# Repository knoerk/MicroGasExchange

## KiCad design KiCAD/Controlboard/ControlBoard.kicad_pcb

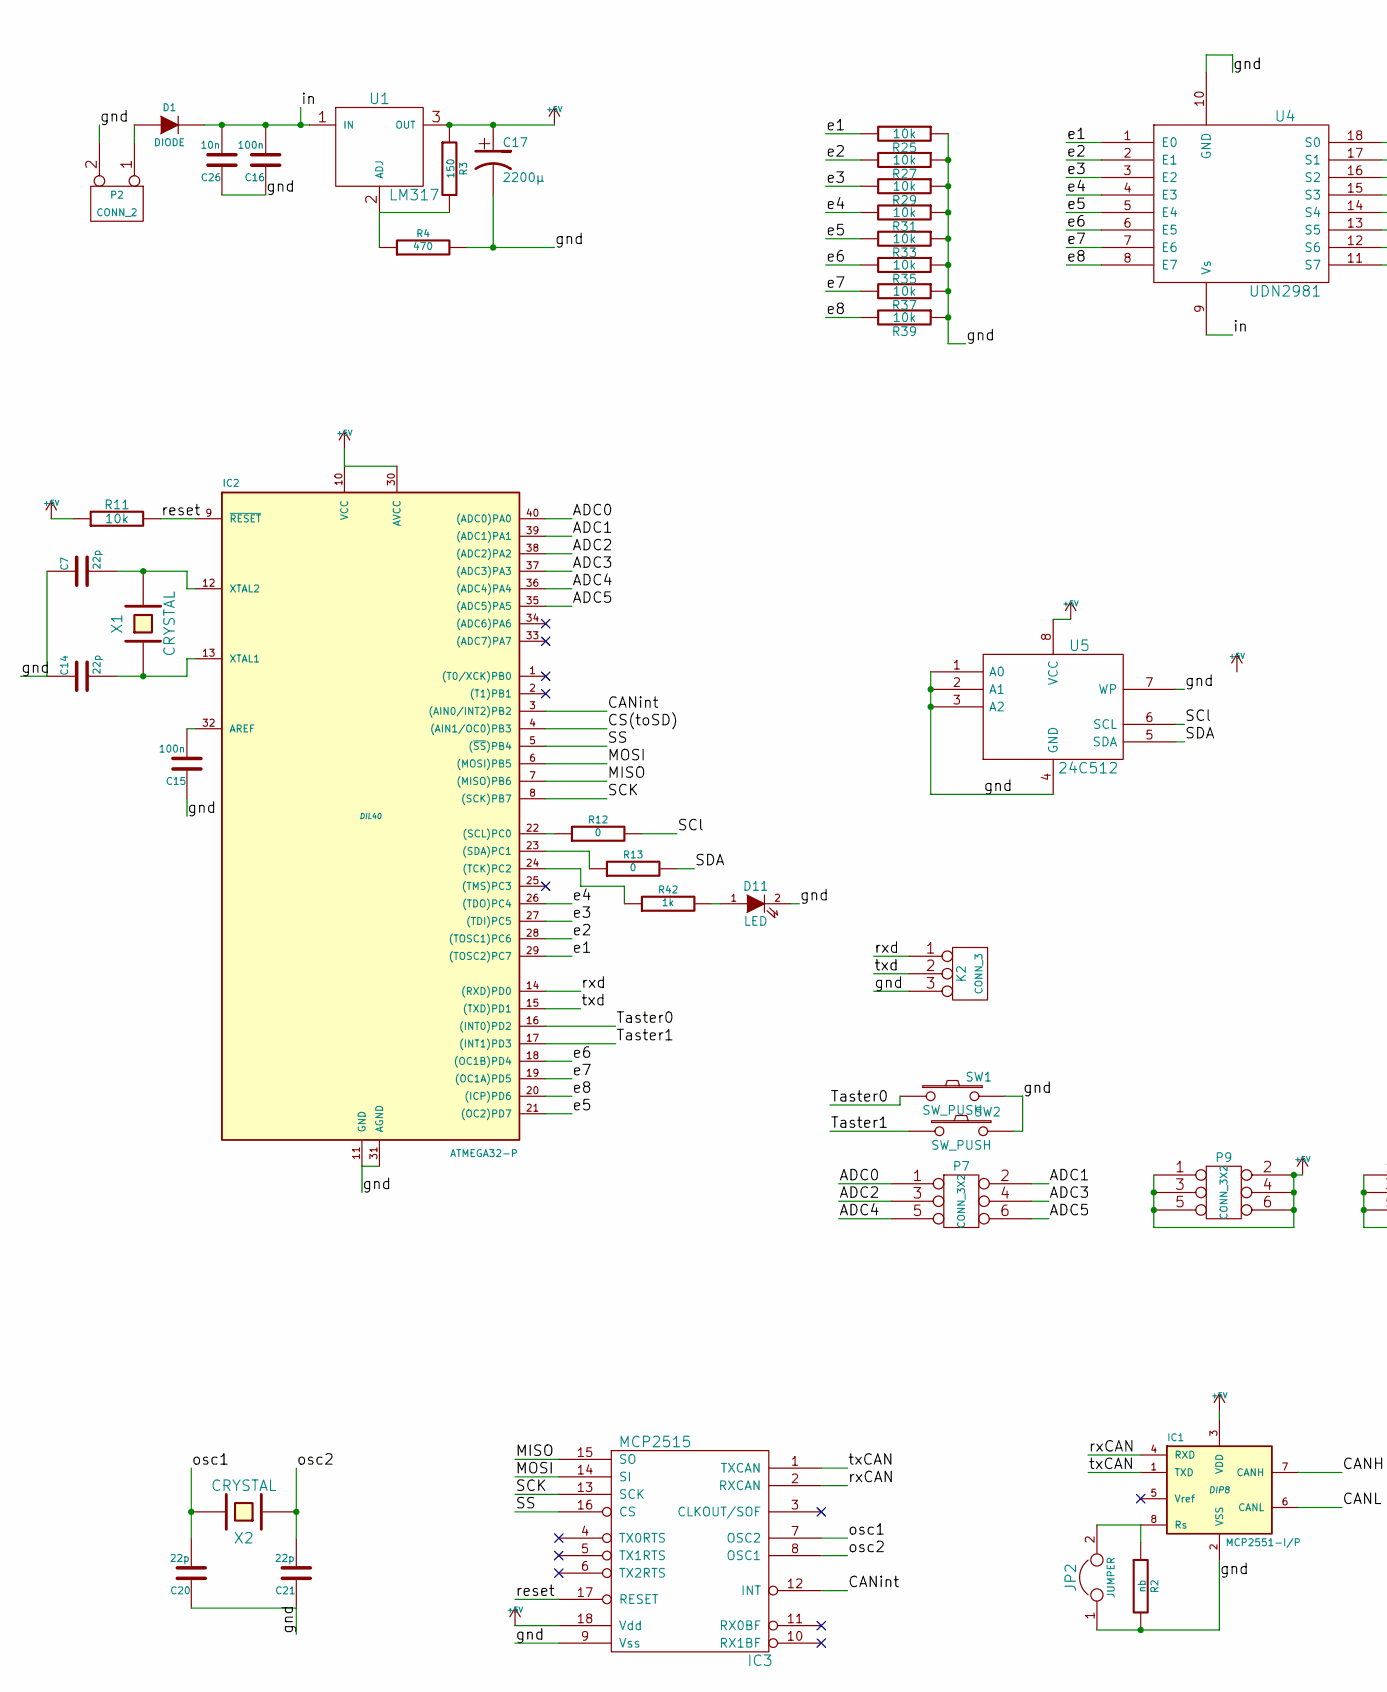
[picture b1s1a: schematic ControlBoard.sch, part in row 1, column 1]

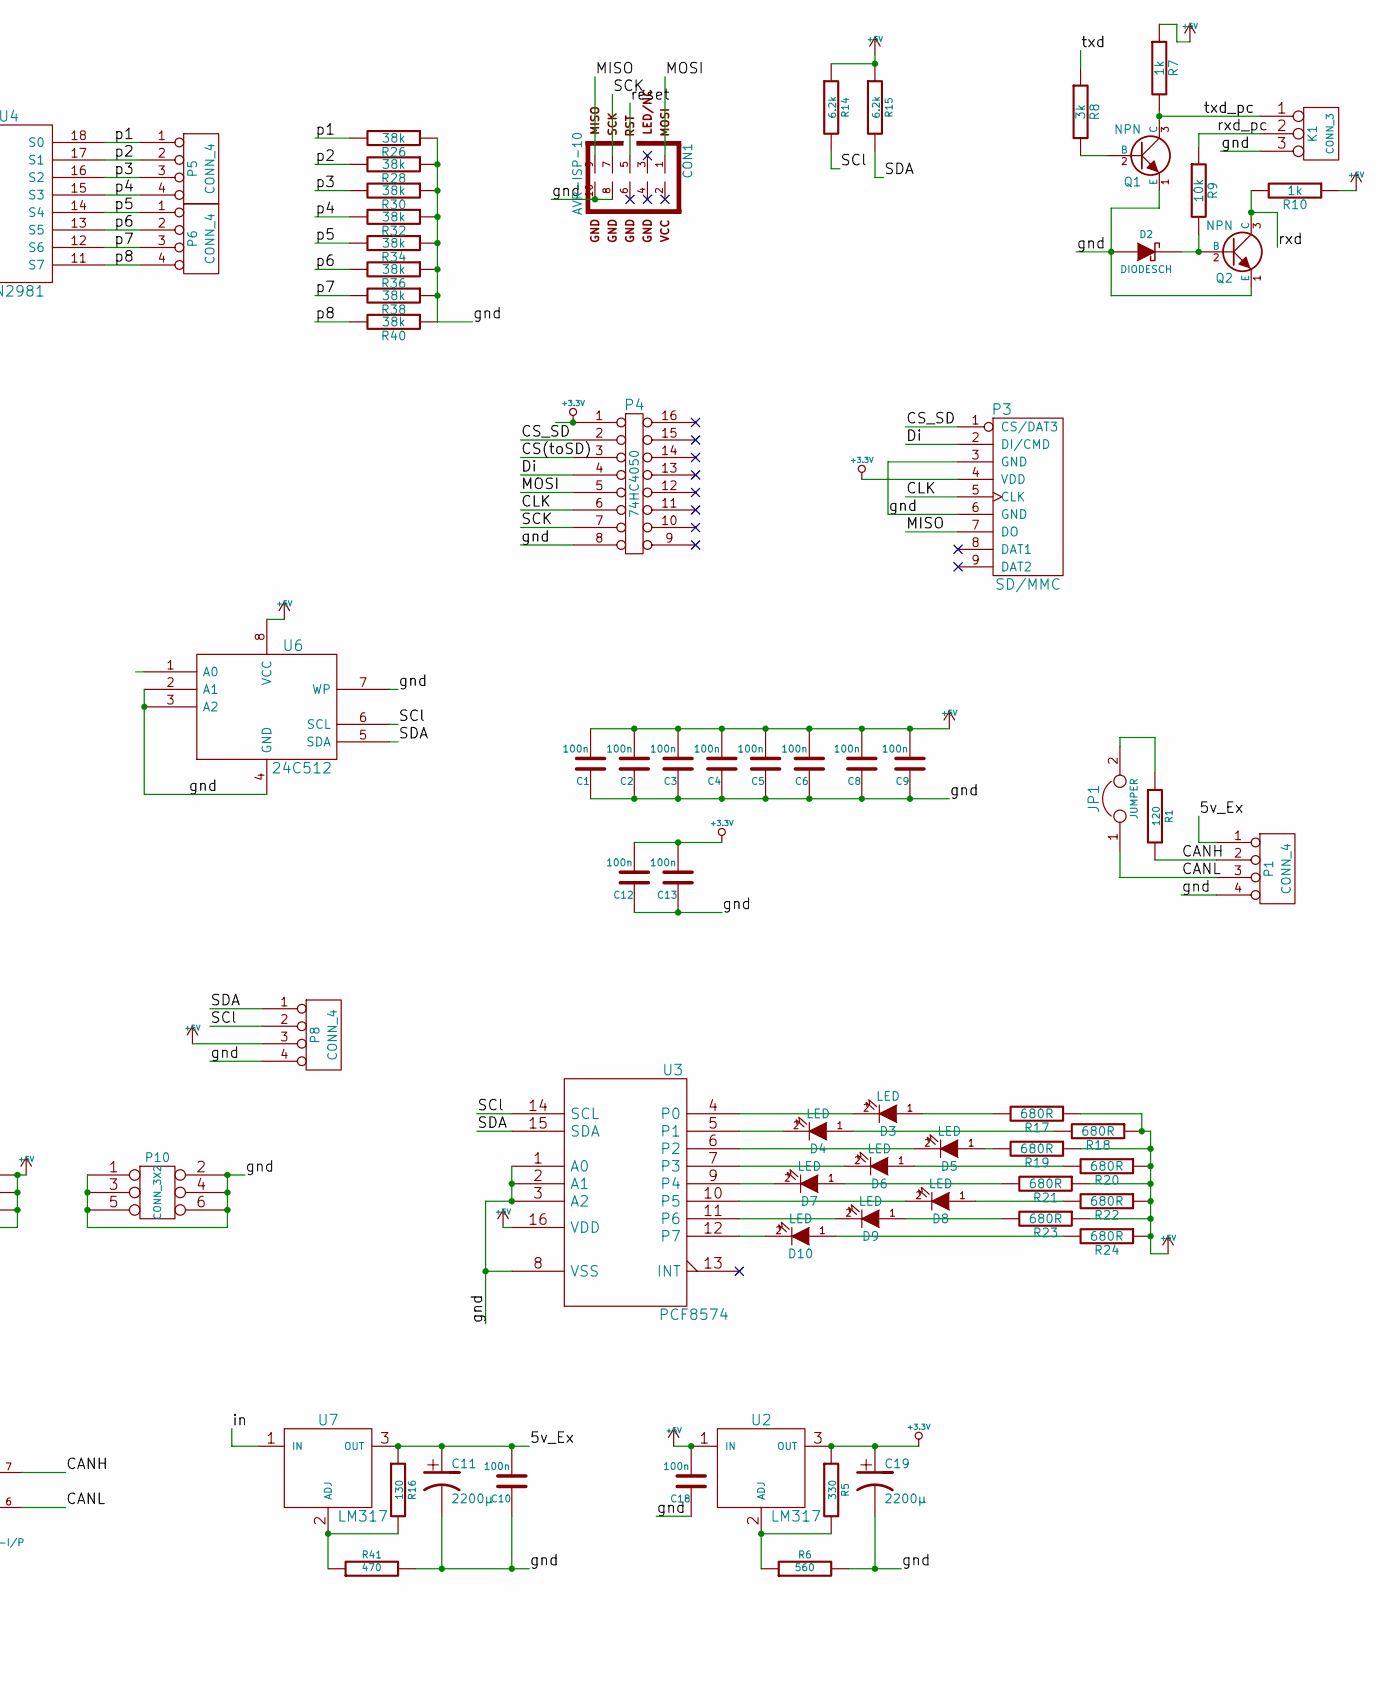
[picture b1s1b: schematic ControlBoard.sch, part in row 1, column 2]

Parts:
C1, C2, C3, C4, C5, C6, C8, C9, C10, C12, C13, C15, C16, C18: 100n
C7, C14, C20, C21: 22p
C11, C17, C19: 2200µ
C26: 10n
CON1: AVR-ISP-10
D1: DIODE
D2: DIODESCH
D3, D4, D5, D6, D7, D8, D9, D10, D11: LED
IC1: MCP2551-I/P; DIP8
IC2: ATMEGA32-P; DIL40
IC3: MCP2515
JP1, JP2: JUMPER
K1, K2: CONN_3
P1, P5, P6, P8: CONN_4
P2: CONN_2
P3: SD/MMC
P4: 74HC4050
P7, P9, P10: CONN_3X2
Q1, Q2: NPN
R1: 120
R2: nb
R3: 150
R4, R41: 470
R5: 330
R6: 560
R7, R10: 1k
R8: 3k
R9, R11, R25, R27, R29, R31, R33, R35, R37, R39: 10k
R12, R13: 0
R14, R15: 6.2k
R16: 130
R17, R18, R19, R20, R21, R22, R23, R24: 680R
R26, R28, R30, R32, R34, R36, R38, R40: 38k
R42: 1k
SW1, SW2: SW_PUSH
U1, U2, U7: LM317
U3: PCF8574
U4: UDN2981
U5, U6: 24C512
X1, X2: CRYSTAL

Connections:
+3.3V: C12.2, C13.2, C19.1, P3.4 (VDD), P4.1, R5.1, U2.3 (OUT)
+5V: C1.2, C2.2, C3.2, C4.2, C5.2, C6.2, C8.2, C9.2, C17.1, C18.2, IC1.3 (VDD), IC2.10 (VCC), IC2.30 (AVCC), IC3.18 (Vdd), P8.3, P9.1, P9.2, P9.3, P9.4, P9.5, P9.6, R3.1, R7.1, R10.1, R11.1, R14.1, R15.1, R17.1, R18.1, R19.1, R20.1, R21.1, R22.1, R23.1, R24.1, U1.3 (OUT), U2.1 (IN), U3.16 (VDD), U5.8 (VCC), U6.1 (A0), U6.8 (VCC)
/5v_Ex: C10.2, C11.1, P1.1, R16.1, U7.3 (OUT)
/ADC0: IC2.40 ((ADC0)PA0), P7.1
/ADC1: IC2.39 ((ADC1)PA1), P7.2
/ADC2: IC2.38 ((ADC2)PA2), P7.3
/ADC3: IC2.37 ((ADC3)PA3), P7.4
/ADC4: IC2.36 ((ADC4)PA4), P7.5
/ADC5: IC2.35 ((ADC5)PA5), P7.6
/CANH: IC1.7 (CANH), P1.2, R1.2
/CANL: IC1.6 (CANL), JP1.1, P1.3
/CANint: IC2.3 ((AIN0/INT2)PB2), IC3.12 (INT)
/CLK: P3.5 (CLK), P4.6
/CS(toSD): IC2.4 ((AIN1/OC0)PB3), P4.3
/CS_SD: P3.1 (CS/DAT3), P4.2
/Di: P3.2 (DI/CMD), P4.4
/MISO: CON1.9, IC2.7 ((MISO)PB6), IC3.15 (SO), P3.7 (DO)
/MOSI: CON1.1, IC2.6 ((MOSI)PB5), IC3.14 (SI), P4.5
/SCK: CON1.7, IC2.8 ((SCK)PB7), IC3.13 (SCK), P4.7
/SCl: P8.2, R12.2, R14.2, U3.14 (SCL), U5.6 (SCL), U6.6 (SCL)
/SDA: P8.1, R13.2, R15.2, U3.15 (SDA), U5.5 (SDA), U6.5 (SDA)
/SS: IC2.5 ((~SS~)PB4), IC3.16 (CS)
/Taster0: IC2.16 ((INT0)PD2), SW1.1
/Taster1: IC2.17 ((INT1)PD3), SW2.1
/e0: IC2.29 ((TOSC2)PC7), R25.2, U4.1 (E0)
/e1: IC2.28 ((TOSC1)PC6), R27.2, U4.2 (E1)
/e2: IC2.27 ((TDI)PC5), R29.2, U4.3 (E2)
/e3: IC2.26 ((TDO)PC4), R31.2, U4.4 (E3)
/e4: IC2.21 ((OC2)PD7), R33.2, U4.5 (E4)
/e5: IC2.18 ((OC1B)PD4), R35.2, U4.6 (E5)
/e6: IC2.19 ((OC1A)PD5), R37.2, U4.7 (E6)
/e7: IC2.20 ((ICP)PD6), R39.2, U4.8 (E7)
/gnd: C1.1, C2.1, C3.1, C4.1, C5.1, C6.1, C7.1, C8.1, C9.1, C10.1, C11.2, C12.1, C13.1, C14.1, C15.1, C16.1, C17.2, C18.1, C19.2, C20.1, C21.1, C26.1, CON1.8, CON1.10, D2.1 (A), D11.2 (K), IC1.2 (VSS), IC2.11 (GND), IC2.31 (AGND), IC3.9 (Vss), JP2.1, K1.3, K2.3, P1.4, P2.2 (PM), P3.3 (GND), P3.6 (GND), P4.8, P8.4, P10.1, P10.2, P10.3, P10.4, P10.5, P10.6, Q1.1 (E), Q2.1 (E), R2.2, R4.2, R6.2, R25.1, R26.1, R27.1, R28.1, R29.1, R30.1, R31.1, R32.1, R33.1, R34.1, R35.1, R36.1, R37.1, R38.1, R39.1, R40.1, R41.2, SW1.2, SW2.2, U3.1 (A0), U3.2 (A1), U3.3 (A2), U3.8 (VSS), U4.10 (GND), U5.1 (A0), U5.2 (A1), U5.3 (A2), U5.4 (GND), U5.7 (WP), U6.2 (A1), U6.3 (A2), U6.4 (GND), U6.7 (WP)
/in: C16.2, C26.2, D1.2 (K), U1.1 (IN), U4.9 (Vs), U7.1 (IN)
/osc1: C20.2, IC3.7 (OSC2), X2.2
/osc2: C21.2, IC3.8 (OSC1), X2.1
/p1: P5.1, R26.2, U4.18 (S0)
/p2: P5.2, R28.2, U4.17 (S1)
/p3: P5.3, R30.2, U4.16 (S2)
/p4: P5.4, R32.2, U4.15 (S3)
/p5: P6.1, R34.2, U4.14 (S4)
/p6: P6.2, R36.2, U4.13 (S5)
/p7: P6.3, R38.2, U4.12 (S6)
/p8: P6.4, R40.2, U4.11 (S7)
/reset: CON1.5, IC2.9 (~RESET), IC3.17 (RESET), R11.2
/rxCAN: IC1.4 (RXD), IC3.2 (RXCAN)
/rxd: IC2.14 ((RXD)PD0), K2.1, Q2.3 (C), R10.2
/rxd_pc: K1.2 (PM), R9.1
/txCAN: IC1.1 (TXD), IC3.1 (TXCAN)
/txd: IC2.15 ((TXD)PD1), K2.2 (PM), R8.1
/txd_pc: K1.1, Q1.3 (C), R7.2
unnamed: D6.2 (K), U3.7 (P3)
unnamed: D7.1 (A), R21.2
unnamed: D7.2 (K), U3.9 (P4)
unnamed: D8.1 (A), R22.2
unnamed: D8.2 (K), U3.10 (P5)
unnamed: D9.1 (A), R23.2
unnamed: D9.2 (K), U3.11 (P6)
unnamed: D10.1 (A), R24.2
unnamed: D10.2 (K), U3.12 (P7)
unnamed: D3.2 (K), U3.4 (P0)
unnamed: D4.2 (K), U3.5 (P1)
unnamed: D5.2 (K), U3.6 (P2)
unnamed: D3.1 (A), R17.2
unnamed: D4.1 (A), R18.2
unnamed: D5.1 (A), R19.2
unnamed: D6.1 (A), R20.2
unnamed: IC2.22 ((SCL)PC0), R12.1
unnamed: IC2.23 ((SDA)PC1), R13.1
unnamed: IC2.24 ((TCK)PC2), R42.1
unnamed: D11.1 (A), R42.2
unnamed: R16.2, R41.1, U7.2 (ADJ)
unnamed: JP1.2, R1.1
unnamed: R3.2, R4.1, U1.2 (ADJ)
unnamed: R5.2, R6.1, U2.2 (ADJ)
unnamed: C14.2, IC2.13 (XTAL1), X1.1
unnamed: C7.2, IC2.12 (XTAL2), X1.2
unnamed: D1.1 (A), P2.1
unnamed: Q1.2 (B), R8.2
unnamed: D2.2 (K), Q2.2 (B), R9.2
unnamed: IC1.8 (Rs), JP2.2, R2.1
unnamed: C15.2, IC2.32 (AREF)

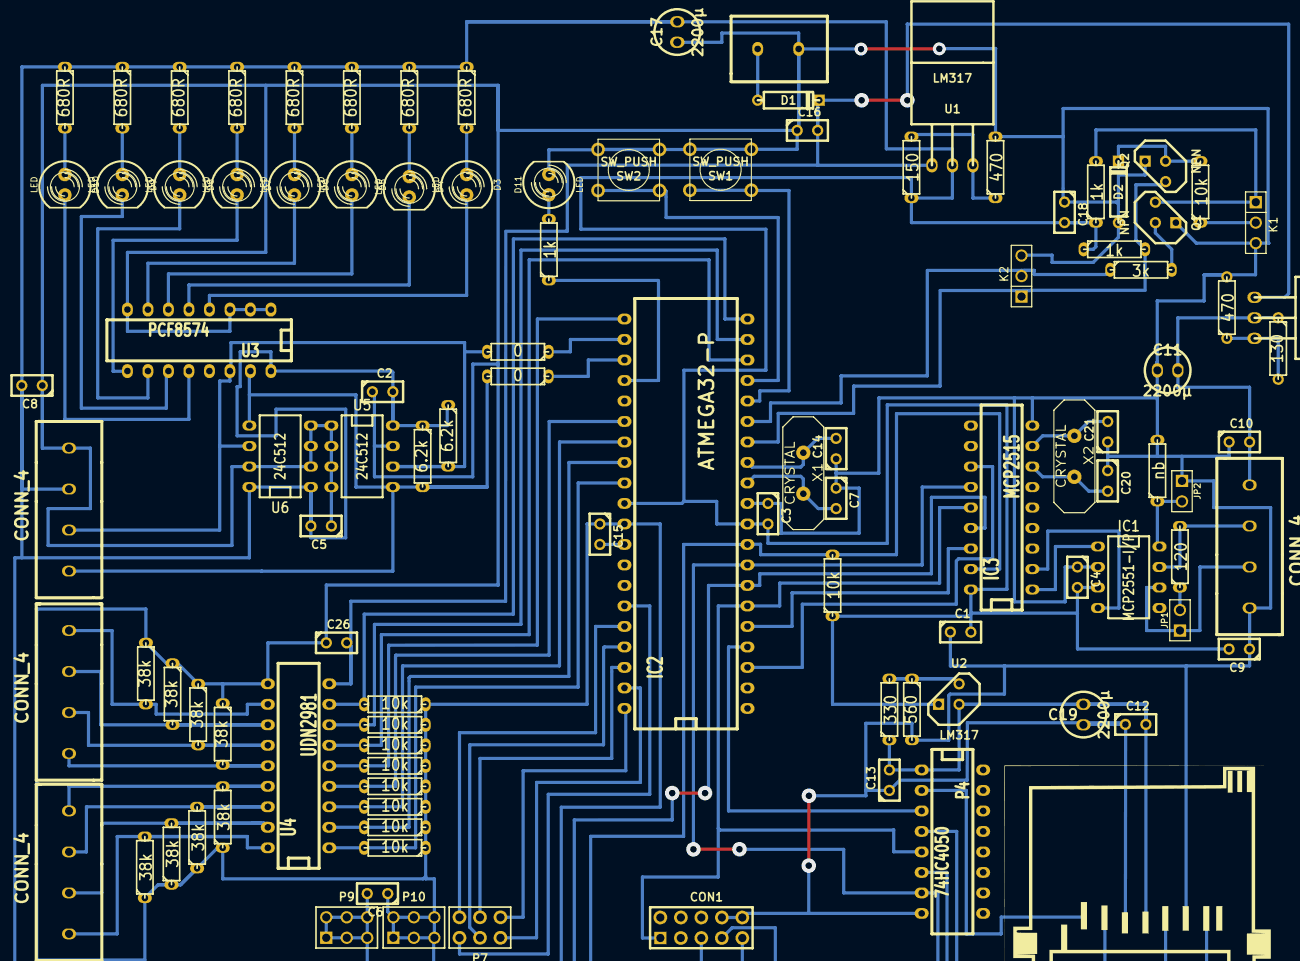
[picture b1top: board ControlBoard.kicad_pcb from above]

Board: 2 copper layers, 106 parts (0 on the bottom side), 82 nets.

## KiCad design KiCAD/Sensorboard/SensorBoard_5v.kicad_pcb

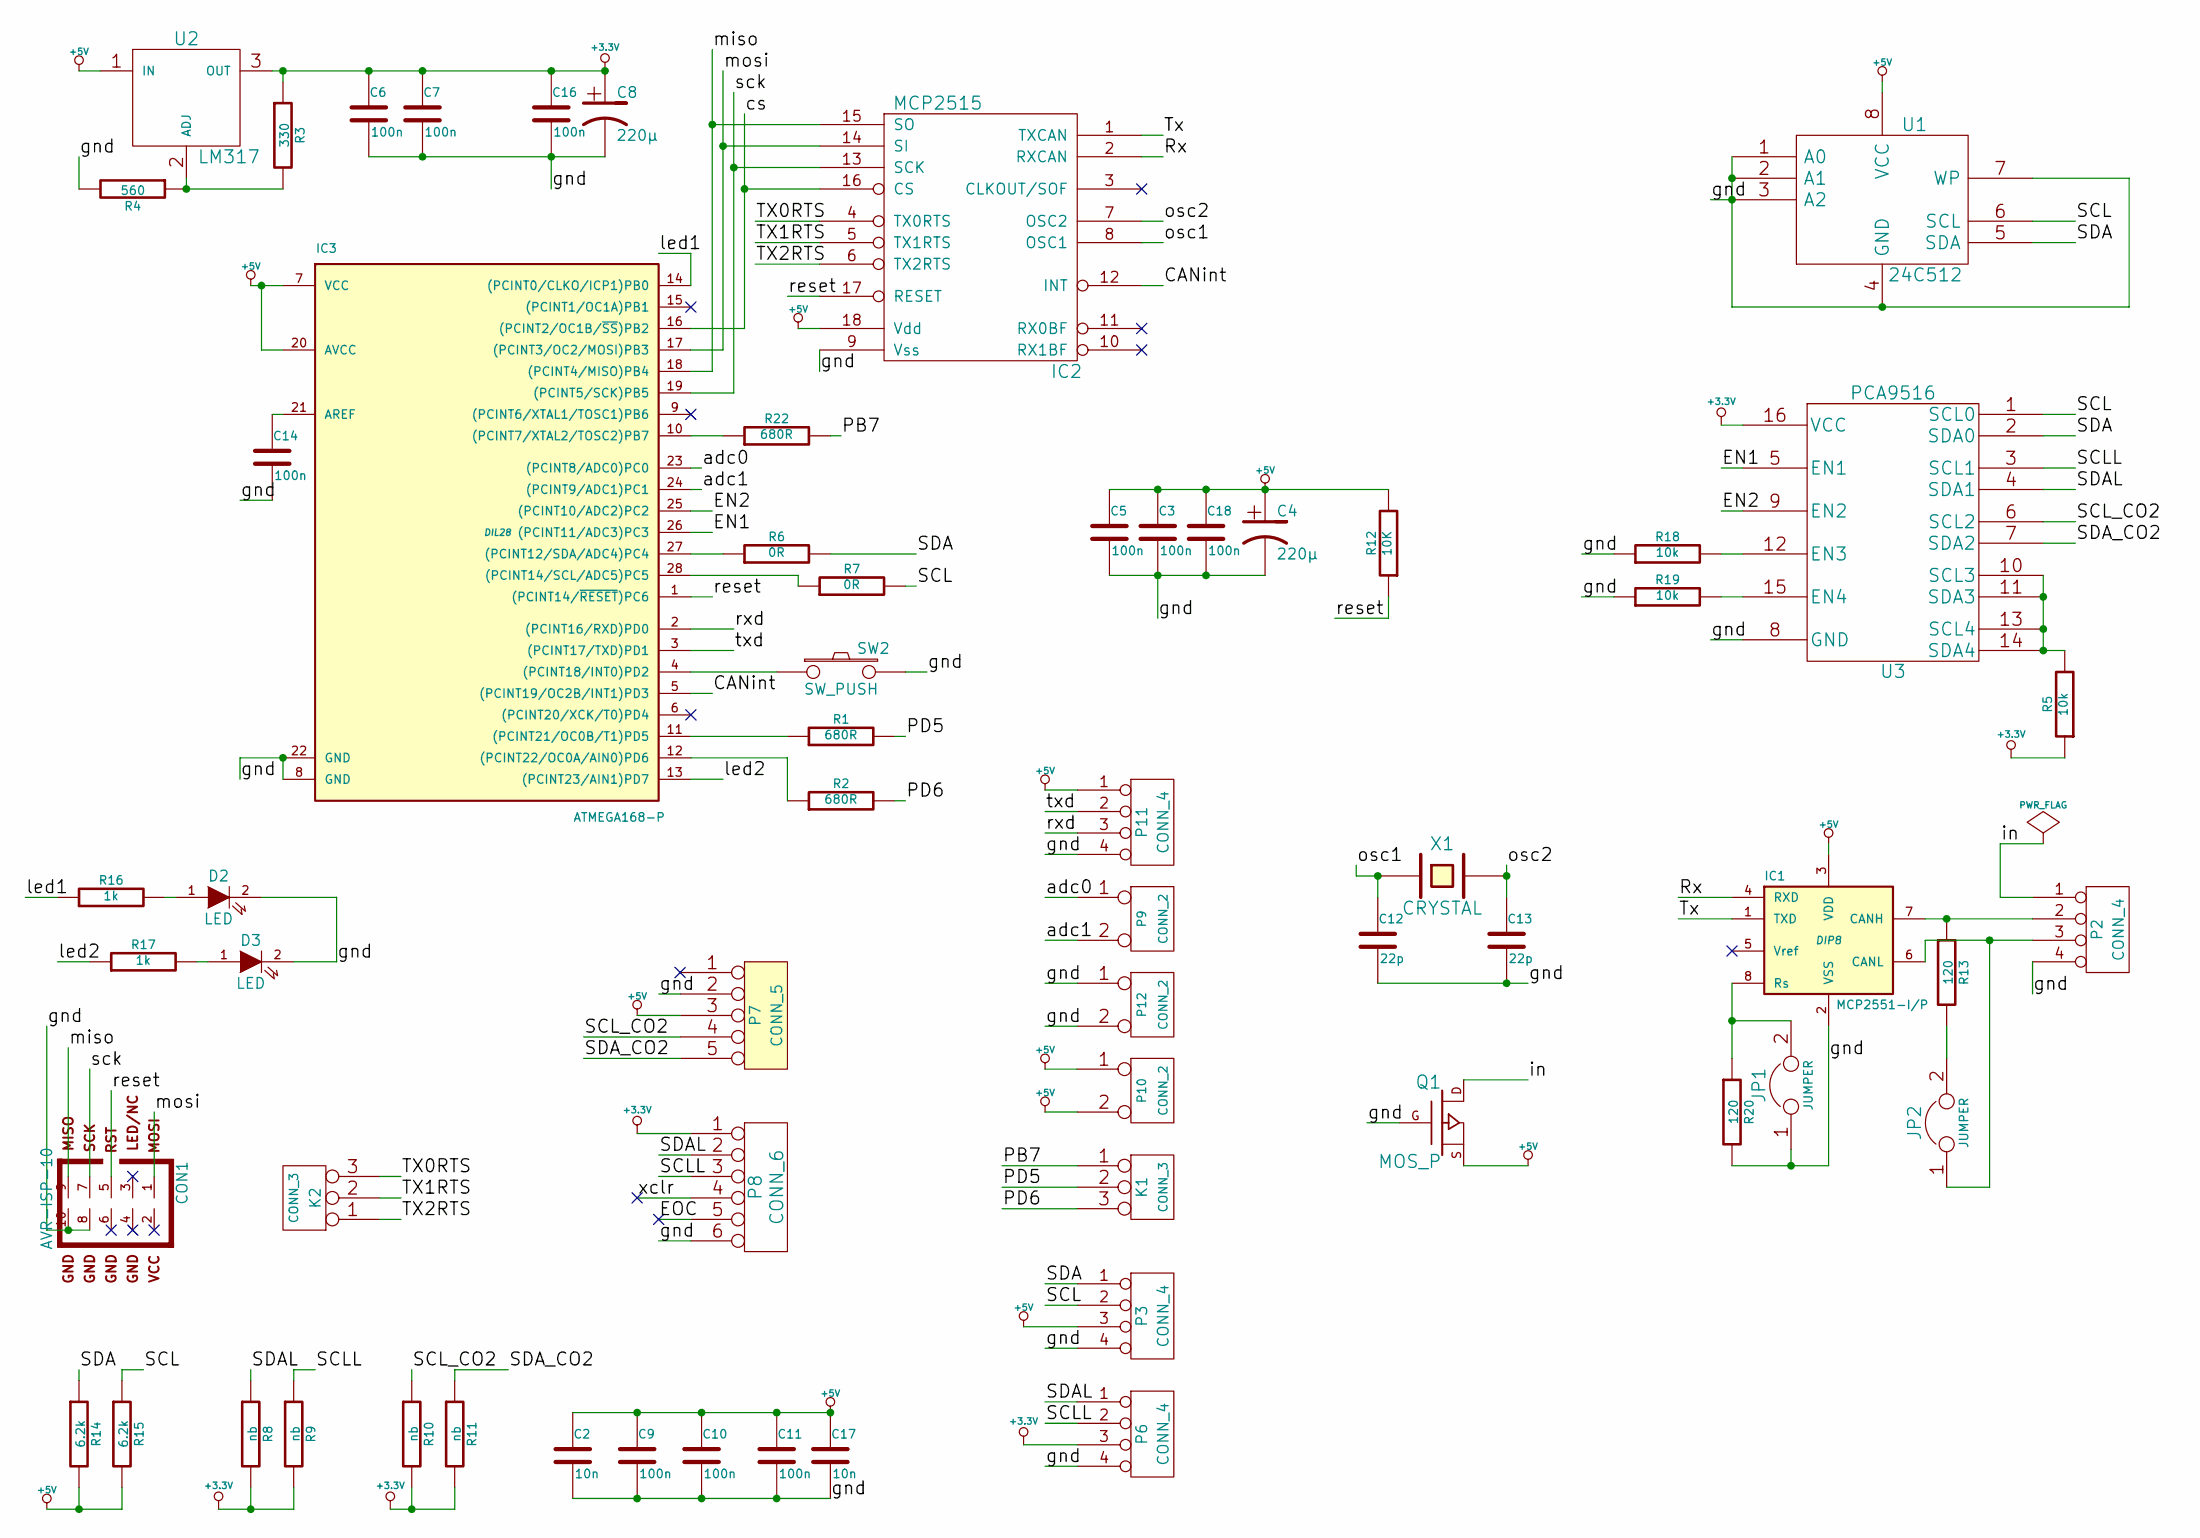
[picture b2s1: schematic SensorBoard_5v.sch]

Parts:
C2, C17: 10n
C3, C5, C6, C7, C9, C10, C11, C14, C16, C18: 100n
C4, C8: 220µ
C12, C13: 22p
CON1: AVR-ISP-10
D2, D3: LED
IC1: MCP2551-I/P; DIP8
IC2: MCP2515
IC3: ATMEGA168-P; DIL28
JP1, JP2: JUMPER
K1, K2: CONN_3
P2, P3, P6, P11: CONN_4
P7: CONN_5
P8: CONN_6
P9, P10, P12: CONN_2
Q1: MOS_P
R1, R2, R22: 680R
R3: 330
R4: 560
R5, R18, R19: 10k
R6, R7: 0R
R8, R9, R10, R11: nb
R12: 10K
R13, R20: 120
R14, R15: 6.2k
R16, R17: 1k
SW2: SW_PUSH
U1: 24C512
U2: LM317
U3: PCA9516
X1: CRYSTAL

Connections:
+3.3V: C6.1, C7.1, C8.1, C16.1, P6.3, P8.1, R3.1, R5.1, R8.2, R9.2, R10.2, R11.2, U2.3 (OUT), U3.16 (VCC)
+5V: C2.1, C3.1, C4.1, C5.1, C9.1, C10.1, C11.1, C17.1, C18.1, IC1.3 (VDD), IC2.18 (Vdd), IC3.7 (VCC), IC3.20 (AVCC), P3.3, P7.3, P10.1, P10.2 (PM), P11.1, Q1.S, R12.2, R14.2, R15.2, U1.8 (VCC), U2.1 (IN)
/CANint: IC2.12 (INT), IC3.5 ((PCINT19/OC2B/INT1)PD3)
/EN1: IC3.26 ((PCINT11/ADC3)PC3), U3.5 (EN1)
/EN2: IC3.25 ((PCINT10/ADC2)PC2), U3.9 (EN2)
/PB7: K1.1, R22.2
/PD5: K1.2 (PM), R1.2
/PD6: K1.3, R2.2
/Rx: IC1.4 (RXD), IC2.2 (RXCAN)
/SCL: P3.2, R7.2, R15.1, U1.6 (SCL), U3.1 (SCL0)
/SCLL: P6.2, P8.3, R9.1, U3.3 (SCL1)
/SCL_CO2: P7.4, R10.1, U3.6 (SCL2)
/SDA: P3.1, R6.2, R14.1, U1.5 (SDA), U3.2 (SDA0)
/SDAL: P6.1, P8.2, R8.1, U3.4 (SDA1)
/SDA_CO2: P7.5, R11.1, U3.7 (SDA2)
/TX0RTS: IC2.4 (TX0RTS), K2.3
/TX1RTS: IC2.5 (TX1RTS), K2.2 (PM)
/TX2RTS: IC2.6 (TX2RTS), K2.1
/Tx: IC1.1 (TXD), IC2.1 (TXCAN)
/adc0: IC3.23 ((PCINT8/ADC0)PC0), P9.1
/adc1: IC3.24 ((PCINT9/ADC1)PC1), P9.2 (PM)
/cs: IC2.16 (CS), IC3.16 ((PCINT2/OC1B/~SS~)PB2)
/gnd: C2.2, C3.2, C4.2, C5.2, C6.2, C7.2, C8.2, C9.2, C10.2, C11.2, C12.2, C13.2, C14.2, C16.2, C17.2, C18.2, CON1.8, CON1.10, D2.2 (K), D3.2 (K), IC1.2 (VSS), IC2.9 (Vss), IC3.8 (GND), IC3.22 (GND), JP1.1, P2.4, P3.4, P6.4, P7.2, P8.6, P11.4, P12.1, P12.2 (PM), Q1.G, R4.2, R18.1, R19.1, R20.2, SW2.2, U1.1 (A0), U1.2 (A1), U1.3 (A2), U1.4 (GND), U1.7 (WP), U3.8 (GND)
/in: P2.1, Q1.D
/led1: IC3.14 ((PCINT0/CLKO/ICP1)PB0), R16.1
/led2: IC3.13 ((PCINT23/AIN1)PD7), R17.1
/miso: CON1.9, IC2.15 (SO), IC3.18 ((PCINT4/MISO)PB4)
/mosi: CON1.1, IC2.14 (SI), IC3.17 ((PCINT3/OC2/MOSI)PB3)
/osc1: C12.1, IC2.8 (OSC1), X1.1
/osc2: C13.1, IC2.7 (OSC2), X1.2
/reset: CON1.5, IC2.17 (RESET), IC3.1 ((PCINT14/~RESET~)PC6), R12.1
/rxd: IC3.2 ((PCINT16/RXD)PD0), P11.3
/sck: CON1.7, IC2.13 (SCK), IC3.19 ((PCINT5/SCK)PB5)
/txd: IC3.3 ((PCINT17/TXD)PD1), P11.2
unnamed: R18.2, U3.12 (EN3)
unnamed: R19.2, U3.15 (EN4)
unnamed: D2.1 (A), R16.2
unnamed: D3.1 (A), R17.2
unnamed: IC3.4 ((PCINT18/INT0)PD2), SW2.1
unnamed: R5.2, U3.10 (SCL3), U3.11 (SDA3), U3.13 (SCL4), U3.14 (SDA4)
unnamed: IC3.11 ((PCINT21/OC0B/T1)PD5), R1.1
unnamed: IC3.27 ((PCINT12/SDA/ADC4)PC4), R6.1
unnamed: IC3.28 ((PCINT14/SCL/ADC5)PC5), R7.1
unnamed: IC3.12 ((PCINT22/OC0A/AIN0)PD6), R2.1
unnamed: IC3.10 ((PCINT7/XTAL2/TOSC2)PB7), R22.1
unnamed: IC1.8 (Rs), JP1.2, R20.1
unnamed: R3.2, R4.1, U2.2 (ADJ)
unnamed: C14.1, IC3.21 (AREF)
unnamed: IC1.7 (CANH), P2.2, R13.1
unnamed: JP2.2, R13.2
unnamed: IC1.6 (CANL), JP2.1, P2.3

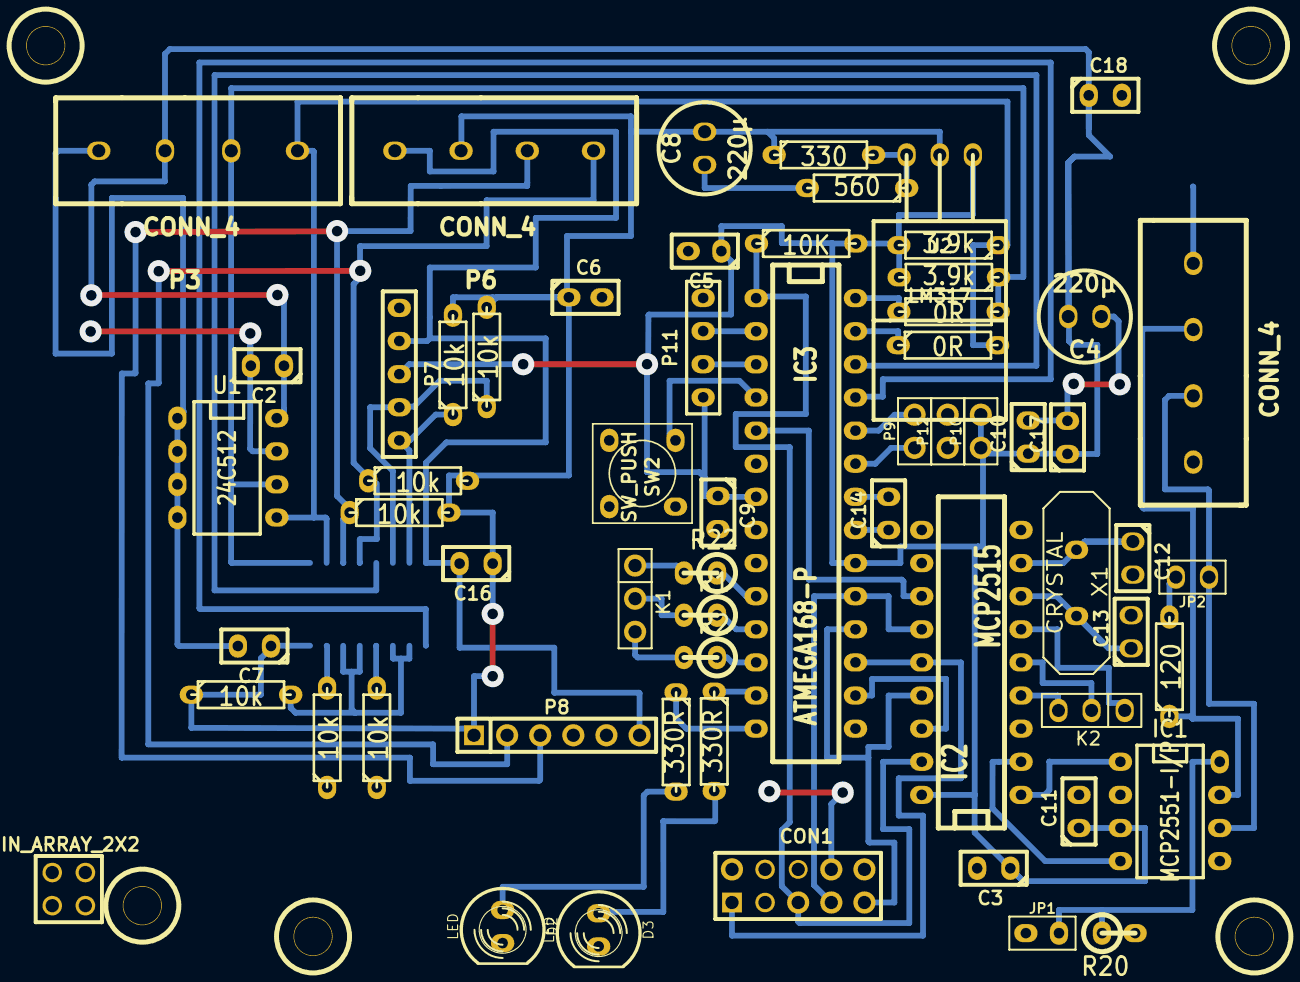
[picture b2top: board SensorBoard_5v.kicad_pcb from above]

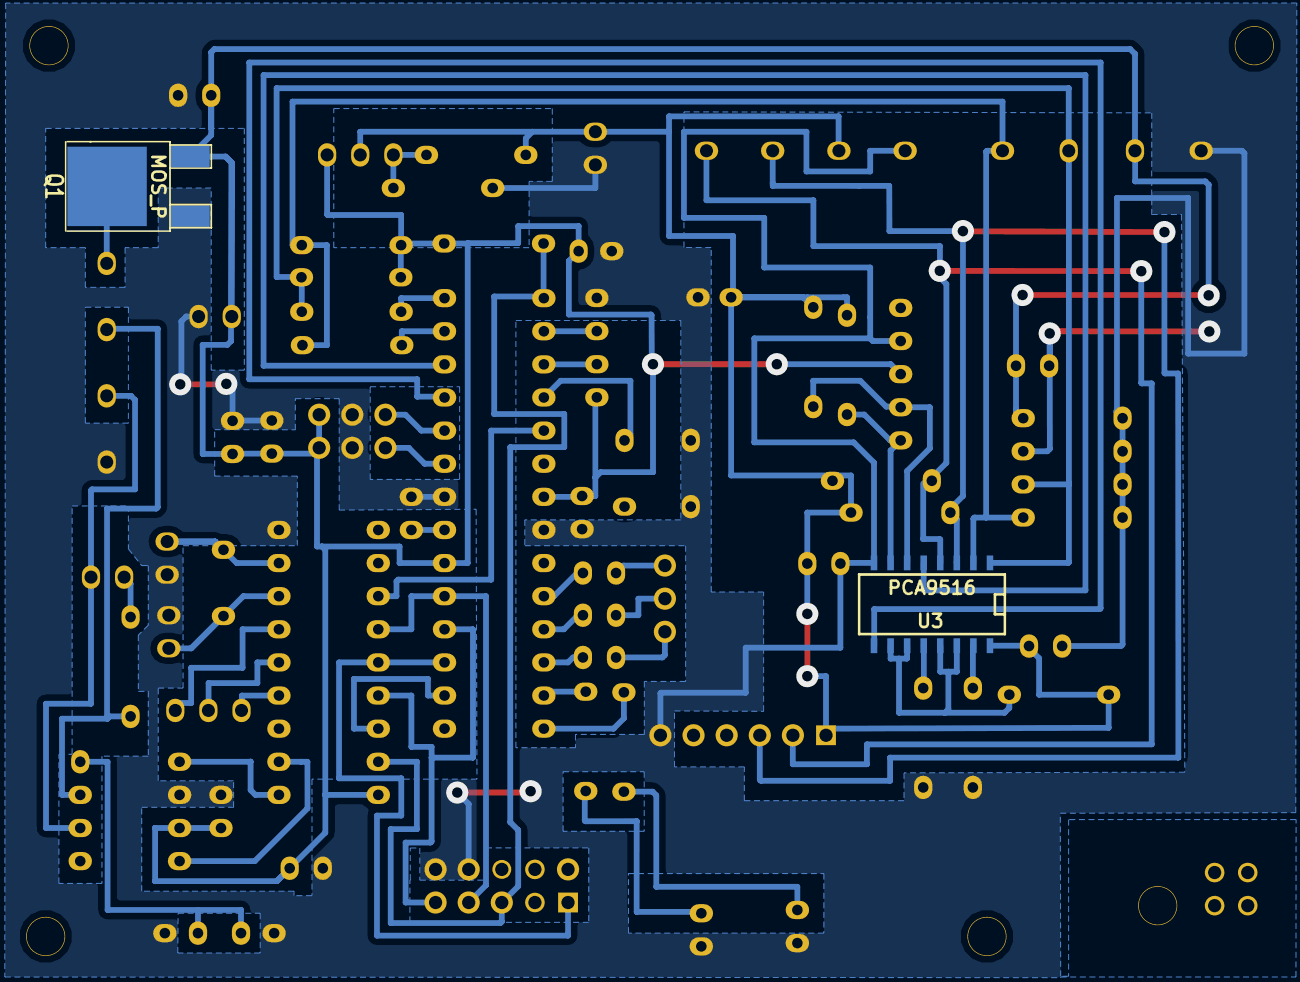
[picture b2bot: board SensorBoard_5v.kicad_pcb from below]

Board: 2 copper layers, 63 parts (2 on the bottom side), 51 nets.

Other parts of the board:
PIN_ARRAY_2X2: Val**; PIN_ARRAY_2X2

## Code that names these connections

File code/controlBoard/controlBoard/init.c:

#include "include/controlBoard.h"

void init ()
{
	//Timer0 fuer Zeit:
	TCCR0 |= (1<<WGM01);
	TCCR0 |= ( (1<<CS01));// | (1<<CS00) );		//clkT2S/64
	TIMSK |= (1<<OCIE0);
	OCR0 = 125;
	
	//Timer1 fuer Heiz innen und aussen
	TCCR1A |= (1<<COM1A1) | (1<<COM1B1) | (1<<WGM10); //PWM phase correct 8-bit; Clear OC1A+OC1B on compare match when up-counting
	TCCR1B |= (1<<CS10) | (1<<CS12);				//Prescaler = 1024
	OCR1A=0;
	OCR1B=0;
	
	//Timer2 fuer Feucht
	TCCR2 |= (1<<WGM20) | (1<<COM21) | (1<<CS21) ; //PWM phase correct ; Clear OC2 on compare match when up-counting, PS = 8
	OCR2=0;
	
	//Timer3:
	TIMER3.TCNT=0;
	TIMER3.OCRA=0;
	TIMER3.OCRB=0;
	TIMER3.OCRC=0;
	TIMER3.OCRD=100;
	
	//Can Interrupt:
	DDRB  &= ~(1<<DDB2);
	GICR |= (1<<INT2) ;
	MCUCSR &= ~(1<<ISC2);
	
	
	//Taster Interrupt:
	DDRD  &= ~(1<<DDD2) | (1<<DDD3);
	PORTD |=  (1<<PD2) | (1<<PD3);
	MCUCR |= (1<<ISC00) | (1<<ISC01) | (1<<ISC10) | (1<<ISC11);
	GICR |= (1<<INT0) | (1<<INT1);
	
	//Outputs:
	DDRD |= ( (1<<DDD4) | (1<<DDD5) | (1<<DDD6) | (1<<DDD7) );
	DDRC |= ( (1<<DDC2) | (1<<DDC4) | (1<<DDC5) | (1<<DDC6) | (1<<DDC7) );
	
	PORTD &= ~( (1<< PD4) | (1<< PD5) | (1<< PD6) | (1<< PD7) );
	PORTC &= ~( (1<< PC4) | (1<< PC5) | (1<< PC6) | (1<< PC7) );
	
	PORTD |= (1<< PD7);
	PORTC |= (1<< PC2);
	//ADC-Pins
	//PINC  &= ~(1<<PC0);
	//PINC  &= ~(1<<PC1);
	//DDRC   &= ~(1<<DDC0);
	//DDRC   &= ~(1<<DDC1);

	//ADC-VRef
	ADMUX  |=  (1<<REFS0) ;
	ADMUX  &=  ~(1<<REFS1) ;
	ADCSRA |= (1<<ADPS0) | (1<<ADPS1) | (1<<ADPS2) ;
	
	
	entprellsperre=0;
	HUMmode=specHum_in;
	
	init_PID_values(&PID_values_preHeat,48,2,92,0,0,250,1,32,0);  //OCRA1
	init_PID_values(&PID_values_inHeat,64,1,512,0,0,250,1,32,0);	//OCR1B
	init_PID_values(&PID_values_specHum_in,8,0,1,0,10,10000,1,128,0);	//OCR2
	init_PID_values(&PID_values_vpd_in,12,0,128,6000,10,2000,1,16,1);	//OCR2
	init_PID_values(&PID_values_co2,5,1,3,10,10,3500,1,64,0);
		
	sei();
	
	uart_init(8);
	twi_init();
	spi_init();
	delay(1);
	mcp2515_init(0,0);
				
	AC1=0;
	AC2=0;
	AC3=0;
	AC4=0;
	AC5=0;
	AC6=0;
	B1=0;
	B2=0;
	MB=0;
	MC=0;
	MD=0;

	PCF8574_byte=0;
	
	can_new_message=0;
	can_new_interrupt=0;
	buffer_update_flag=0;
	
	treatment=0;
	repetition=0;
	tick=1;
	saveToEpromEnabled=0;
	memoryAdress=64;
	CanErrorStatus=0;
	
	sTime.days=0;
	sTime.daySecs=1;
	sTime.daySecsTEMP=0;
}

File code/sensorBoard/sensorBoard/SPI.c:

#include "include/SPI.h"

void spi_init()
{
	// Aktivieren der Pins für das SPI Interface
	
	DDRB   |= (1<<DDB2);
	PORTB  |= (1<<PB2);	
	
	DDRB  |= (1<<DDB3) | (1<<DDB5);
	PORTB &= ~( (1<<PB3) | (1<<PB4) | (1<<PB5) );
	

	
	// Aktivieren des SPI Master Interfaces, fosc = fclk / 16
	SPCR = ( (1<<SPE) | (1<<MSTR)  |(0<<SPR0) );
	SPSR = (1<<SPI2X);
}


uint8_t spi_put_c( uint8_t data )
{
		while( ( SPSR & (1<<SPIF) ) )
		{
		}
	
		SPDR = data;

		while( !( SPSR & (1<<SPIF) ) )
		{
		}
				
		return SPDR;
}

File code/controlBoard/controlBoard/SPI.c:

#include "include/SPI.h"

void spi_init()
{
	// Aktivieren der Pins für das SPI Interface
	
	DDRB   |= (1<<DDB4);
	PORTB  |= (1<<PB4);	
	
	DDRB  |= (1<<DDB5) | (1<<DDB7);
	PORTB &= ~( (1<<PB5) | (1<<PB6) | (1<<PB7) );
	

	
	// Aktivieren des SPI Master Interfaces, fosc = fclk / 16
	SPCR = ( (1<<SPE) | (1<<MSTR)  |(0<<SPR0) );
	SPSR = (1<<SPI2X);
}


uint8_t spi_put_c( uint8_t data )
{
		while( ( SPSR & (1<<SPIF) ) )
		{
		}
	
		SPDR = data;

		while( !( SPSR & (1<<SPIF) ) )
		{
		}
				
		return SPDR;
}

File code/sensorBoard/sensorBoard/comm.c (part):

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	{
		data[0]=238;
		data[1]=0xAA;
		PORTC |= (1<<PC3);
		values=i2c_comm(data, 2,22,1);
		PORTC &= ~(1<<PC3);

		AC1 = (int16_t)( ( ( (uint16_t)(values[0]) )<<8 ) | values[1] );
		AC2 = (int16_t)( ( ( (uint16_t)(values[2]) )<<8 ) | values[3] );
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	data[0]=238;
	data[1]=0xE0;
	data[2]=0xB6;
	PORTC |= (1<<PC3);
	i2c_comm(data, 2,0,0);
	PORTC &= ~(1<<PC3);
}

void bmp_get_values(volatile int16_t *temp,volatile int32_t *pressure)
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	data[1]=0xF4;
	data[2]=0x2E;
	TWBR = 1;
	PORTC |= (1<<PC3);
	
	uint8_t count=0;
	do
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	} while (I2CBuffer.succesBit && (count<3) );


	PORTC &= ~(1<<PC3);
	if (I2CBuffer.succesBit==0)
	{
		ATOMIC_BLOCK(ATOMIC_RESTORESTATE)
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uint8_t k30_get_values(volatile int16_t* co,volatile uint8_t* status)
{
	TWBR = 16;
	PORTC |= (1<<PC2);

	volatile uint8_t data[5];
	data[0]=208;
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	} while ( (I2CBuffer.succesBit) && (milisecCounter3 < 200) );

	
	PORTC &= ~(1<<PC2);
	TWBR = 1;

	
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
uint8_t hyt_change_adress(uint8_t address_o, uint8_t adress_n)
{
	//sensor  (+) must be connected to ADC1 pin (PC1)
	DDRC |= (1<<DDC1);
	PORTC &= ~(1<<PC1);
	simple_delay(100);
	PORTC |= (1<<PC1);
	simple_delay(1);
	comm_mode_hyt(address_o);
	adress_n=adress_n>>1;
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uint8_t read_meter_control_from_k30()
{
	TWBR = 16;
	PORTC |= (1<<PC2);
	
	uint8_t *values;
	volatile uint8_t data[6];
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	values=i2c_comm(data,0,3,0);  //read status, data bytes and checksum
	//uint8_t checkSum = values[0]+values[1];

	PORTC &= ~(1<<PC2);
	TWBR = 1;
	
	if (I2CBuffer.succesBit != 0)
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uint8_t write_meter_control_to_k30(uint8_t mConNew)
{
	TWBR = 16;
	PORTC |= (1<<PC2);
	simple_delay(30);
	volatile uint8_t data[6];
	uint8_t *values=0;
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	simple_delay(30);
	data[0]=208;
	values=i2c_comm(data,0,2,0);  //read status and checksum
	PORTC &= ~(1<<PC2);
	TWBR = 1;
	
	if (I2CBuffer.succesBit != 0)
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
uint8_t handleCanMessage(volatile sensValues* acualVales)
{
	PORTB ^=  (1<<PB0);
	CANMessage inMessage;
	
	if (can_get_message(&inMessage) != 0xff)
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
